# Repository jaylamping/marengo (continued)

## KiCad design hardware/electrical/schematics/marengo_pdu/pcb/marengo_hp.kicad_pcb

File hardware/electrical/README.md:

# Electrical

Power distribution, harnessing, and field bus topology for Marengo.

- [`pdb/`](pdb/) — Power Distribution Board (KiCad schematic, layout, BOM)
- [`wiring/`](wiring/) — Harness runs, CAN layout, connector pinouts

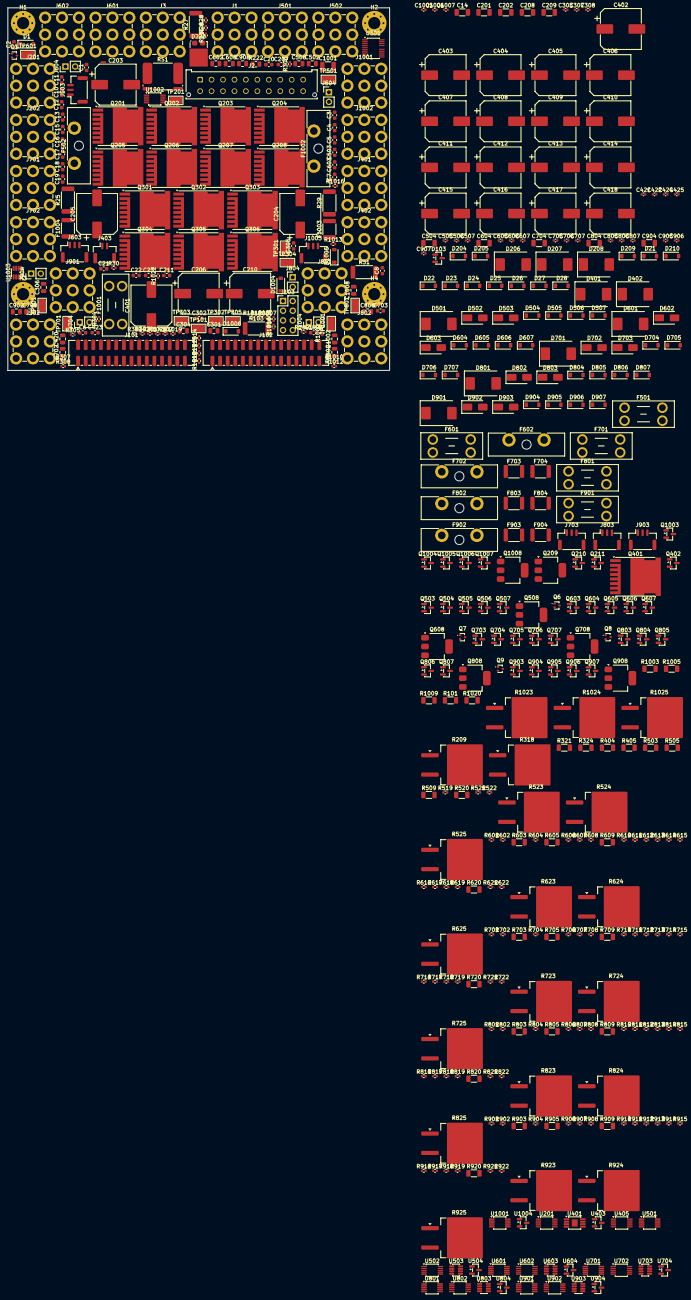
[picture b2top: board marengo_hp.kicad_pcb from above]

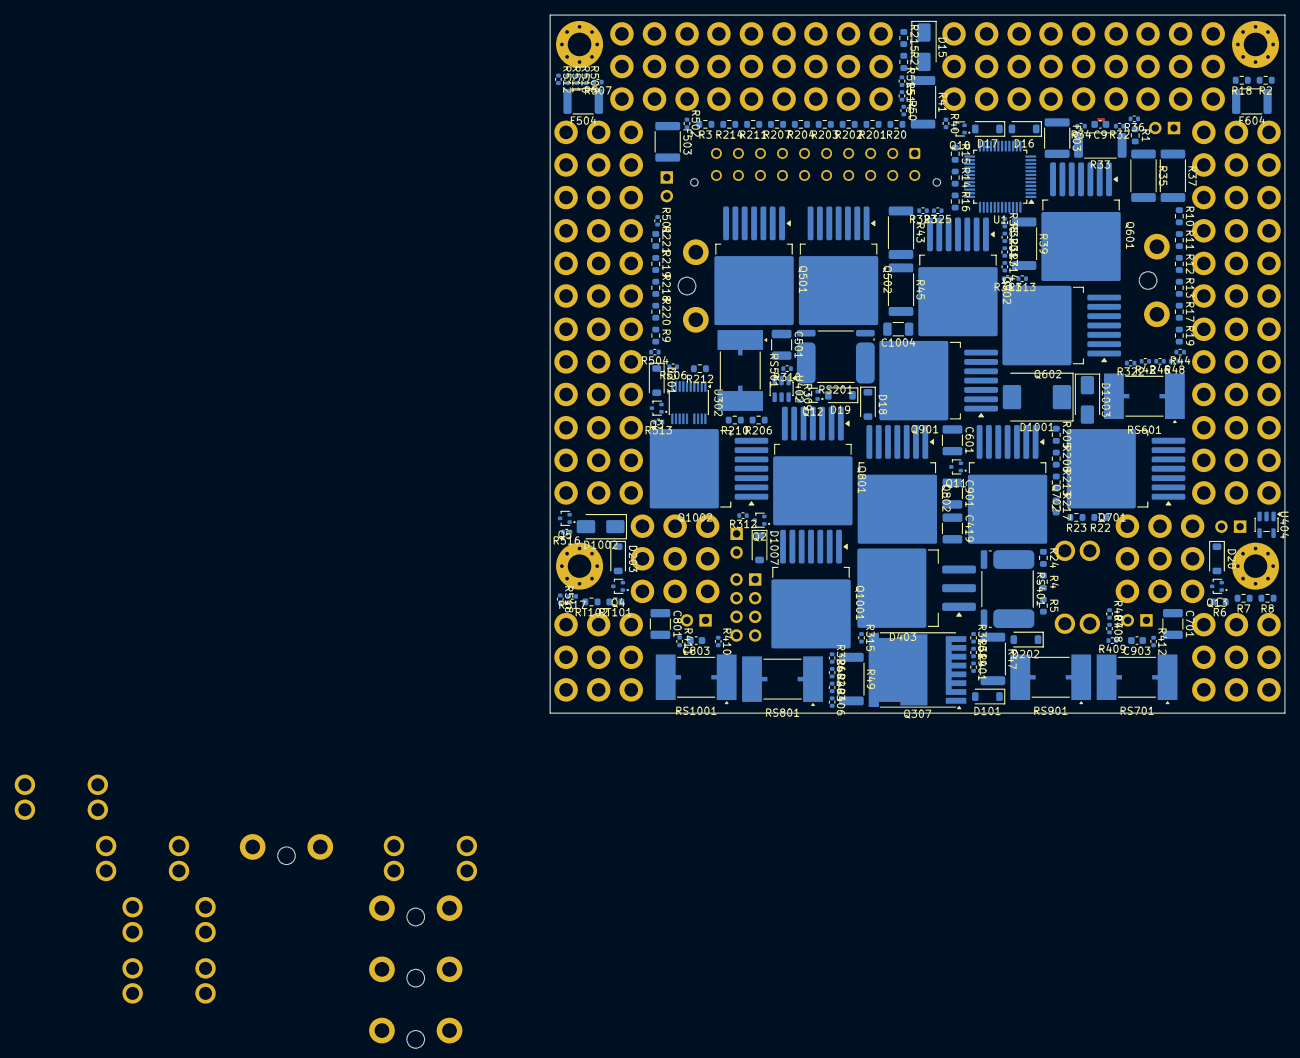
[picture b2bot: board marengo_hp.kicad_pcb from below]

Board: 4 copper layers, 100.0 x 95.0 mm, 653 parts (166 on the bottom side), 373 nets, no tracks yet.

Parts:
C1, C2, C3, C4, C5, C6, C7, C8, C9, C10, C11, C12: 220nF; C_0603_1608Metric
C13, C17, C207: 100nF; C_0603_1608Metric
C14: 1uF 100V; C_1206_3216Metric
C15, C18: 100pF; C_0603_1608Metric
C16: 1uF; C_0603_1608Metric
C19: 2.2uF; C_0603_1608Metric
C20, C21, C22, C211: 1nF; C_0603_1608Metric
C23, C302, C305: 1uF 25V X7R; C_0603_1608Metric
C201, C202, C208, C209: 100nF 100V; C_1206_3216Metric
C203, C204, C205, C206, C210, C401, C402, C403, C404, C405, C406, C407, C408, C409, C410, C411, C412, C413, C414, C415, C416, C417, C418: 100uF 80V HHXF800GRA101MJH0G; CP_Elec_10x14.3
C301, C304, C306, C502, C602, C702, C802, C902, C1002: 100nF 100V; C_0805_2012Metric
C303: 680pF C0G; C_0402_1005Metric
C307, C308: 1nF; C_0402_1005Metric
C419, C501, C601, C701, C801, C901, C1001: 1uF 100V; C_1210_3225Metric
C420: 4.7uF 25V; C_0805_2012Metric
C421: 100pF C0G; C_0402_1005Metric
C422, C424, C425, C505, C506, C507, C605, C606, C607, C705, C706, C707, C805, C806, C807, C905, C906, C907, C1005, C1006, C1007: 100nF; C_0402_1005Metric
C423: 1uF 25V; C_0603_1608Metric
C503, C603, C703, C803, C903, C1003: 100nF C0G; C_0603_1608Metric
C504, C604, C704, C804, C904, C1004: 47nF 100V C0G; C_1206_3216Metric
C508, C608, C708, C808, C908, C1008: 4.7nF 100V; C_0805_2012Metric
D1: BAV19W 120V; D_SOD-123
D15: SS14-E3/61T 40V 1A; D_SMA
D16, D17, D18, D19, D20, D21, D22, D23, D24, D25, D26, D27, D28: BZT52C5V1; D_SOD-123
D101: MMSZ4684 3.3V; D_SOD-123
D103: BAT54C; SOT-23
D201, D203, D204: MMSZ5246B 16V; D_SOD-123
D202, D205, D209, D504, D604, D704, D804, D904, D1004: BAV19W; D_SOD-123
D206, D207, D401, D402: SMDJ58A; D_SMC
D208: SMDJ58CA; D_SMC
D210: MMSZ4685 3.6V; D_SOD-123
D220: V10PM15-M3/I 150V 10A; TO-277A
D403: MBRB30H100CT-E3/81; TO-263-3_TabPin2
D501, D601, D701, D801, D901, D1001: MBRS3100T3G; D_SMC
D502, D503, D602, D603, D702, D703, D802, D803, D902, D903, D1002, D1003: SMAJ58CA; D_SMA
D505, D605, D705, D805, D905, D1005: MMSZ5242B 12V; D_SOD-123
D506, D507, D606, D607, D706, D707, D806, D807, D906, D907, D1006, D1007: MMSZ5246B; D_SOD-123
F501, F601, F701, F801, F901, F1001: 20A 58V 0997020.WXN; Fuseholder_Blade_Mini_Keystone_3568
F502, F602, F702, F802, F902, F1002: leg fuse, format open; Fuseholder_Blade_ATO_Littelfuse_Pudenz_2_Pin
F503, F603, F703, F803, F903, F1003: 0.14A MF-MSMF014/60X; Fuse_1812_4532Metric
F504, F604, F704, F804, F904, F1004: 0.10A MF-MSMF010/60X; Fuse_1812_4532Metric
H1, H2, H3, H4: M3 standoff; MountingHole_3.2mm_M3_Pad_Via
J1, J3: M4 terminal, REDCUBE 74651194R; Wuerth_REDCUBE-THR_WP-THRSH_74651194_THR
J2: 2x10 locking header; Molex_Micro-Fit_3.0_43045-2012_2x10_P3.00mm_Vertical
J101: 2x15 2 mm box, power and logic; Molex_8783230xx_2x15_P2.0mm_Header_Vertical_Polarized
J102: 2x15 2 mm box, CAN and analog; Molex_8783230xx_2x15_P2.0mm_Header_Vertical_Polarized
J103: CAN fault injection, CAN6; PinHeader_2x04_P2.54mm_Vertical
J201: M4 terminal, charger +, 74651194R; Wuerth_REDCUBE-THR_WP-THRSH_74651194_THR
J202: M4 terminal, charger -, 74651194R; Wuerth_REDCUBE-THR_WP-THRSH_74651194_THR
J401: M4 terminal, Arcol HS25 10R +; Wuerth_REDCUBE-THR_WP-THRSH_74651194_THR
J402: M4 terminal, Arcol HS25 10R -; Wuerth_REDCUBE-THR_WP-THRSH_74651194_THR
J403: brake R NTC; JST_GH_SM02B-GHS-TB_1x02-1MP_P1.25mm_Horizontal
J501, J601, J701, J801, J901, J1001: M4 terminal, port +; Wuerth_REDCUBE-THR_WP-THRSH_74651194_THR
J502, J602, J702, J802, J902, J1002: M4 terminal, port -; Wuerth_REDCUBE-THR_WP-THRSH_74651194_THR
J503, J603, J703, J803, J903, J1003: CAN to trunk; JST_GH_SM03B-GHS-TB_1x03-1MP_P1.25mm_Horizontal
J504, J604, J704, J804, J904, J1004: term jumper; PinHeader_1x02_P2.54mm_Vertical
NT1: Net-Tie; NetTie-2_SMD_Pad0.5mm
Q1, Q2, Q3, Q4, Q5, Q6, Q7, Q8, Q9, Q10, Q11, Q12, Q13: SSM3K56FS; SOT-416
Q201, Q202, Q203, Q204, Q205, Q206, Q207, Q208, Q301, Q302, Q303, Q304, Q305, Q306, Q307, Q401: IPT015N10N5; Infineon_PG-HSOF-8-1
Q209: DMP10H400SE; SOT-223-3_TabPin2
Q210, Q402, Q503, Q504, Q506, Q507, Q603, Q604, Q606, Q607, Q703, Q704, Q706, Q707, Q803, Q804, Q806, Q807, Q903, Q904, Q906, Q907, Q1003, Q1004, Q1006, Q1007: BSS123; SOT-23
Q211: MMBT2907A; SOT-23
Q501, Q502, Q601, Q602, Q701, Q702, Q801, Q802, Q901, Q902, Q1001, Q1002: IPB017N10N5LFATMA1; TO-263-7_TabPin4
Q505, Q605, Q705, Q805, Q905, Q1005: MMBTA92 PNP; SOT-23
Q508, Q608, Q708, Q808, Q908, Q1008: DMP10H400SE-13; SOT-223-3_TabPin2
R1: 20R; R_0603_1608Metric
R2, R3, R4, R5, R6, R7, R8, R9, R10, R11, R12, R13, R14, R15, R16, R17: 100R; R_0603_1608Metric
R18, R19, R20, R21, R211, R213, R214: 5.1k; R_0603_1608Metric
R22: 1k; R_0603_1608Metric
R23, R24, R219: 10k; R_0603_1608Metric
R25, R27, R29, R31, R33, R35, R37, R39, R41, R43, R45, R47, R49: 27R 1W 2512; R_2512_6332Metric
R26, R28, R30, R32, R34, R36, R38, R40, R42, R44, R46, R48, R50, R508, R608, R708, R808, R908, R1008: 1k; R_0402_1005Metric
R101, R509, R520, R609, R620, R709, R720, R809, R820, R909, R920, R1009, R1020: 1M; R_1206_3216Metric
R102, R302, R303, R306, R308, R309, R311, R409, R510, R610, R710, R810, R910, R1010: 100k; R_0402_1005Metric
R103: 100R 1W; R_2512_6332Metric
R201, R202, R203, R204, R205, R206, R207, R208: 4.7R; R_0603_1608Metric
R209, R318: 100R PWR263S-35-1000F; TO-263-2
R210, R220: 1M; R_0603_1608Metric
R212, R217, R218: 10M; R_0603_1608Metric
R215: 220R; R_0603_1608Metric
R216, R522, R622, R722, R822, R922, R1022: 10k; R_0402_1005Metric
R221: 62k; R_0603_1608Metric
R222: 15R; R_0805_2012Metric
R301, R307, R412, R514, R614, R714, R814, R914, R1014: 100R; R_0402_1005Metric
R304, R310, R320, R511, R611, R711, R811, R911, R1011: 1M; R_0402_1005Metric
R305: 10.5k 1%; R_0402_1005Metric
R312, R313, R314, R315, R316, R317: 2.2R; R_0402_1005Metric
R319, R410, R411, R501, R502, R512, R513, R601, R602, R612, R613, R701, R702, R712, R713, R801, R802, R812, R813, R901, R902, R912, R913, R1001, R1002, R1012, R1013: 10R; R_0402_1005Metric
R321, R324: 1M 0.1%; R_1206_3216Metric
R322, R325: 56k 0.1%; R_0402_1005Metric
R323, R326, R515, R615, R715, R815, R915, R1015: 49.9R; R_0402_1005Metric
R401: 464k; R_0402_1005Metric
R402: 49.9k; R_0402_1005Metric
R403: 9.09k; R_0402_1005Metric
R404: 499k 0.1%; R_1206_3216Metric
R405: 604k 0.1%; R_1206_3216Metric
R406: 51.1k 0.1%; R_0402_1005Metric
R407: 19.1M; R_0402_1005Metric
R408: 4.7R; R_0402_1005Metric
R503, R603, R703, R803, R903, R1003: 191k; R_1206_3216Metric
R504, R604, R704, R804, R904, R1004: 18.7k; R_0402_1005Metric
R505, R605, R705, R805, R905, R1005: 95.3k; R_1206_3216Metric
R506, R606, R706, R806, R906, R1006: 4.12k; R_0402_1005Metric
R507, R607, R707, R807, R907, R1007: 69.8k; R_0402_1005Metric
R516, R616, R716, R816, R916, R1016: 25.5k 0.1%; R_0402_1005Metric
R517, R617, R717, R817, R917, R1017: 34.0k 0.1%; R_0402_1005Metric
R518, R618, R718, R818, R918, R1018: 2.61k 0.1%; R_0402_1005Metric
R519, R619, R719, R819, R919, R1019: 3.48M; R_0402_1005Metric
R521, R621, R721, R821, R921, R1021: 33k; R_0402_1005Metric
R523, R623, R723, R823, R923, R1023: 150R PWR263S-35-1500F; TO-263-2
R524, R525, R624, R625, R724, R725, R824, R825, R924, R925, R1024, R1025: 56R PWR263S-35-56R0F; TO-263-2
RS1, RS201: 0.3mR CSS4J-4026 5W; R_Shunt_Isabellenhuette_BVR4026
RS401: 2mR CSS4J-4026K-2L00F 6W; R_Shunt_Isabellenhuette_BVR4026
RS501, RS601, RS701, RS801, RS901, RS1001: 3mR WSLP39213L000FEA 5W; WSLP3921_Kelvin
RT101, RT102: 10k B3435; R_0603_1608Metric
TP101, TP301, TP302, TP303, TP304, TP305, TP501, TP601, TP701, TP801, TP901, TP1001: TP; TestPoint_Keystone_5015_Micro_Mini
TP201: VSYS; TestPoint_Keystone_5015_Micro_Mini
U1: BQ76952PFBR; TQFP-48_7x7mm_P0.5mm
U201, U405, U502, U602, U702, U802, U902, U1002: INA228AIDGSR; TSSOP-10_3x3mm_P0.5mm
U301, U302: TPS48100QDGXRQ1; TPS48100_DGX_VSSOP-19
U401: TPS7A4001DGNR; HVSSOP-8-1EP_3x3mm_P0.65mm_EP1.57x1.89mm
U402: TLV1805DBVR; SOT-23-6
U403: LM4040AIM3-2.5; SOT-23
U404: UCC27517DBVR; SOT-23-5
U501, U601, U701, U801, U901, U1001: LM5069MMX-1; MSOP-10_3x3mm_P0.5mm
U503, U603, U703, U803, U903, U1003: INA241A1IDDFR; SOT-23-8
U504, U604, U704, U804, U904, U1004: TL431BIDBZR; SOT-23

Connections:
+3V3_HP: C207.1, C425.1, C506.1, C507.1, C606.1, C607.1, C706.1, C707.1, C806.1, C807.1, C906.1, C907.1, C1006.1, C1007.1, J101.28, R303.2, R309.2, U201.6, U405.2, U405.6, U502.6, U503.6, U503.7, U602.2, U602.6, U603.6, U603.7, U702.1, U702.6, U703.6, U703.7, U802.6, U803.6, U803.7, U902.1, U902.6, U903.6, U903.7, U1002.1, U1002.2, U1002.6, U1003.6, U1003.7
/HP_power_board/BOARD_NTC: RT101.1, U1.28
/HP_power_board/CHG_GATE: R211.1, U1.45
/HP_power_board/DFETOFF: D103.3, R102.1, U1.30
/HP_power_board/DSG_GATE: D202.1, R213.1, U1.43
/HP_power_board/FI_V: J103.8, R103.2
/HP_power_board/PACK_PRESENT_N: D101.1, D103.1, J2.13, R101.2
/HP_power_board/PACK_TOP: C201.1, C203.1, C204.1, C205.1, C206.1, D1.2, D201.2, D206.1, J1.1, Q201.2, Q202.2, Q203.2, Q204.2, R101.1, R212.2
/HP_power_board/PDSG: Q209.1, R210.2, U1.39
/HP_power_board/V_PORT6: D1007.1, F1001.2, F1002.2, J1001.1, Q1008.3, R103.1, R1014.1, R1016.1, R1020.1, R1022.1, TP1001.1
/HP_power_board/bms_fets_precharge/CD: Q201.3, Q202.3, Q203.3, Q204.3, Q205.3, Q206.3, Q207.3, Q208.3, Q209.3, R210.1
/HP_power_board/bms_fets_precharge/CHG_G: D201.1, R201.1, R202.1, R203.1, R204.1, R211.2, R212.1
/HP_power_board/bms_fets_precharge/CHG_IN: D208.2, D209.2, D220.1, D220.2, J201.1
/HP_power_board/bms_fets_precharge/DSG_G: D203.1, Q210.3, Q211.2, R205.1, R206.1, R207.1, R208.1, R214.2, R216.2, R217.1
/HP_power_board/bms_fets_precharge/DSG_OFF_B: Q211.1, R215.2, R216.1
/HP_power_board/bms_fets_precharge/DSG_OFF_C: Q211.3, R222.1
/HP_power_board/bms_fets_precharge/DSG_OUT: C202.2, D203.2, D204.2, Q205.2, Q206.2, Q207.2, Q208.2, Q210.2, R209.3, R217.2, R218.2, R222.2, RS201.1
/HP_power_board/bms_fets_precharge/PDSG_R: Q209.2, R209.1
/HP_power_board/estop_banks/BST_A: C302.1, U301.12
/HP_power_board/estop_banks/BST_B: C305.1, U302.12
/HP_power_board/estop_banks/FLT_B: R309.1, TP302.1, U302.5
/HP_power_board/estop_banks/G2_B: R319.1, U302.11
/HP_power_board/estop_banks/G2_G: Q307.1, R319.2, R320.1
/HP_power_board/estop_banks/GA0: Q301.1, R312.2
/HP_power_board/estop_banks/GA1: Q303.1, R313.2
/HP_power_board/estop_banks/GA2: Q305.1, R314.2
/HP_power_board/estop_banks/GATE_A: R304.1, R312.1, R313.1, R314.1, U301.14, U301.15
/HP_power_board/estop_banks/GATE_B: R310.1, R315.1, R316.1, R317.1, U302.14, U302.15
/HP_power_board/estop_banks/GB0: Q302.1, R315.2
/HP_power_board/estop_banks/GB1: Q304.1, R316.2
/HP_power_board/estop_banks/GB2: Q306.1, R317.2
/HP_power_board/estop_banks/ISCP_A: R305.1, U301.8
/HP_power_board/estop_banks/MID_DIV: C307.1, R321.2, R322.1, R323.1
/HP_power_board/estop_banks/PRE_D: Q307.3, R318.3
/HP_power_board/estop_banks/TMR_A: C303.1, R306.1, U301.9
/HP_power_board/estop_banks/VMOT_DIV: C308.1, R324.2, R325.1, R326.1
/HP_power_board/estop_banks/VS_A: C301.1, R301.2, U301.20
/HP_power_board/estop_banks/VS_B: C304.1, R307.2, U302.17, U302.18, U302.20
/HP_power_board/pack_input_shunt_afe/B0: D16.2, J2.4, Q1.2, R14.1, R24.1
/HP_power_board/pack_input_shunt_afe/B1: D17.2, J2.14, Q2.2, R13.1, R25.1
/HP_power_board/pack_input_shunt_afe/B2: D18.2, J2.5, Q3.2, R12.1, R27.1
/HP_power_board/pack_input_shunt_afe/B3: D19.2, J2.15, Q4.2, R11.1, R29.1
/HP_power_board/pack_input_shunt_afe/B4: D20.2, J2.6, Q5.2, R10.1, R31.1
/HP_power_board/pack_input_shunt_afe/B5: D21.2, J2.16, Q6.2, R9.1, R33.1
/HP_power_board/pack_input_shunt_afe/B6: D22.2, J2.7, Q7.2, R8.1, R35.1
/HP_power_board/pack_input_shunt_afe/B7: D23.2, J2.17, Q8.2, R7.1, R37.1
/HP_power_board/pack_input_shunt_afe/B8: D24.2, J2.8, Q9.2, R6.1, R39.1
/HP_power_board/pack_input_shunt_afe/B9: D25.2, J2.18, Q10.2, R5.1, R41.1
/HP_power_board/pack_input_shunt_afe/B10: D26.2, J2.9, Q11.2, R4.1, R43.1
/HP_power_board/pack_input_shunt_afe/B11: D27.2, J2.19, Q12.2, R3.1, R45.1
/HP_power_board/pack_input_shunt_afe/B12: D28.2, J2.10, Q13.2, R2.1, R47.1
/HP_power_board/pack_input_shunt_afe/B13: J2.20, R1.1, R49.1
/HP_power_board/pack_input_shunt_afe/BAT: C14.1, C15.1, C16.1, R15.2, U1.47
/HP_power_board/pack_input_shunt_afe/BAT-: J3.1, NT1.1, R24.2, RS1.1
/HP_power_board/pack_input_shunt_afe/BD1: Q1.3, R25.2
/HP_power_board/pack_input_shunt_afe/BD2: Q2.3, R27.2
/HP_power_board/pack_input_shunt_afe/BD3: Q3.3, R29.2
/HP_power_board/pack_input_shunt_afe/BD4: Q4.3, R31.2
/HP_power_board/pack_input_shunt_afe/BD5: Q5.3, R33.2
/HP_power_board/pack_input_shunt_afe/BD6: Q6.3, R35.2
/HP_power_board/pack_input_shunt_afe/BD7: Q7.3, R37.2
/HP_power_board/pack_input_shunt_afe/BD8: Q8.3, R39.2
/HP_power_board/pack_input_shunt_afe/BD9: Q9.3, R41.2
/HP_power_board/pack_input_shunt_afe/BD10: Q10.3, R43.2
/HP_power_board/pack_input_shunt_afe/BD11: Q11.3, R45.2
/HP_power_board/pack_input_shunt_afe/BD12: Q12.3, R47.2
/HP_power_board/pack_input_shunt_afe/BD13: Q13.3, R49.2
/HP_power_board/pack_input_shunt_afe/BG1: D16.1, Q1.1, R26.1
/HP_power_board/pack_input_shunt_afe/BG2: D17.1, Q2.1, R28.1
/HP_power_board/pack_input_shunt_afe/BG3: D18.1, Q3.1, R30.1
/HP_power_board/pack_input_shunt_afe/BG4: D19.1, Q4.1, R32.1
/HP_power_board/pack_input_shunt_afe/BG5: D20.1, Q5.1, R34.1
/HP_power_board/pack_input_shunt_afe/BG6: D21.1, Q6.1, R36.1
/HP_power_board/pack_input_shunt_afe/BG7: D22.1, Q7.1, R38.1
/HP_power_board/pack_input_shunt_afe/BG8: D23.1, Q8.1, R40.1
/HP_power_board/pack_input_shunt_afe/BG9: D24.1, Q9.1, R42.1
/HP_power_board/pack_input_shunt_afe/BG10: D25.1, Q10.1, R44.1
/HP_power_board/pack_input_shunt_afe/BG11: D26.1, Q11.1, R46.1
/HP_power_board/pack_input_shunt_afe/BG12: D27.1, Q12.1, R48.1
/HP_power_board/pack_input_shunt_afe/BG13: D28.1, Q13.1, R50.1
/HP_power_board/pack_input_shunt_afe/CP1: C16.2, U1.46
/HP_power_board/pack_input_shunt_afe/LD_S: R20.1, U1.41
/HP_power_board/pack_input_shunt_afe/NTC1: C20.1, J2.1, U1.21
/HP_power_board/pack_input_shunt_afe/NTC2: C21.1, J2.11, U1.23
/HP_power_board/pack_input_shunt_afe/NTC3: C22.1, J2.2, U1.29
/HP_power_board/pack_input_shunt_afe/PACK_S: R18.1, U1.42
/HP_power_board/pack_input_shunt_afe/SRN: R17.1, RS1.3
/HP_power_board/pack_input_shunt_afe/SRN_F: C17.2, C18.2, R17.2, U1.20
/HP_power_board/pack_input_shunt_afe/SRP: R16.1, RS1.2
/HP_power_board/pack_input_shunt_afe/SRP_F: C17.1, C18.1, R16.2, U1.18
/HP_power_board/pack_input_shunt_afe/TS2_F: R23.1, U1.22
/HP_power_board/pack_input_shunt_afe/VC0: C13.2, C23.1, D15.1, R14.2, R26.2, U1.16
/HP_power_board/pack_input_shunt_afe/VC1: C12.2, C13.1, R13.2, R28.2, U1.15
/HP_power_board/pack_input_shunt_afe/VC2: C11.2, C12.1, R12.2, R30.2, U1.14
/HP_power_board/pack_input_shunt_afe/VC3: C10.2, C11.1, R11.2, R32.2, U1.13
/HP_power_board/pack_input_shunt_afe/VC4: C9.2, C10.1, R10.2, R34.2, U1.12
/HP_power_board/pack_input_shunt_afe/VC5: C8.2, C9.1, R9.2, R36.2, U1.11
/HP_power_board/pack_input_shunt_afe/VC6: C7.2, C8.1, R8.2, R38.2, U1.10
/HP_power_board/pack_input_shunt_afe/VC7: C6.2, C7.1, R7.2, R40.2, U1.9
/HP_power_board/pack_input_shunt_afe/VC8: C5.2, C6.1, R6.2, R42.2, U1.8
/HP_power_board/pack_input_shunt_afe/VC9: C4.2, C5.1, R5.2, R44.2, U1.7
/HP_power_board/pack_input_shunt_afe/VC10: C3.2, C4.1, R4.2, R46.2, U1.6
/HP_power_board/pack_input_shunt_afe/VC11: C2.2, C3.1, R3.2, R48.2, U1.5
/HP_power_board/pack_input_shunt_afe/VC12: C1.2, C2.1, R2.2, R50.2, U1.1, U1.2, U1.3, U1.4
/HP_power_board/pack_input_shunt_afe/VC16: C1.1, R1.2, U1.48
/HP_power_board/port_1_L_ARM/CAN_REF: F503.1, J503.3
/HP_power_board/port_1_L_ARM/CAS_D: Q507.3, R521.1
/HP_power_board/port_1_L_ARM/CAS_G: D506.1, Q507.1, R520.2
/HP_power_board/port_1_L_ARM/CDV: C504.1, D504.1, Q505.2
/HP_power_board/port_1_L_ARM/CDV_B: Q505.1, R508.2
/HP_power_board/port_1_L_ARM/EN_INV: D505.1, Q503.1, Q504.3, R509.2
/HP_power_board/port_1_L_ARM/EN_S: Q504.2, Q506.3
/HP_power_board/port_1_L_ARM/G1: Q501.1, R501.2
/HP_power_board/port_1_L_ARM/G2: Q502.1, R502.2
/HP_power_board/port_1_L_ARM/GATE: D504.2, R501.1, R502.1, R508.1, U501.10
/HP_power_board/port_1_L_ARM/IM_RAW: R515.1, U503.5
/HP_power_board/port_1_L_ARM/IN_N: C505.2, R513.2, U502.9
/HP_power_board/port_1_L_ARM/IN_P: C505.1, R512.2, U502.10
/HP_power_board/port_1_L_ARM/OVLO: R505.2, R506.1, U501.4
/HP_power_board/port_1_L_ARM/PD: Q508.2, R519.1, R523.1
/HP_power_board/port_1_L_ARM/PG: D507.2, Q508.1, R521.2, R522.2
/HP_power_board/port_1_L_ARM/PWR: R507.1, U501.7
/HP_power_board/port_1_L_ARM/Q_D: Q501.4, Q502.4, RS501.4
/HP_power_board/port_1_L_ARM/SH_N: R513.1, RS501.3, U501.1, U503.1
/HP_power_board/port_1_L_ARM/SH_P: C502.1, R512.1, RS501.2, U501.2, U503.8
/HP_power_board/port_1_L_ARM/TERM_J: F504.2, J504.1
/HP_power_board/port_1_L_ARM/TERM_M: C508.1, R524.3, R525.1
/HP_power_board/port_1_L_ARM/TERM_P: F504.1, R525.3
/HP_power_board/port_1_L_ARM/TIMER: C503.1, U501.6
/HP_power_board/port_1_L_ARM/TL_K: Q507.2, U504.1
/HP_power_board/port_1_L_ARM/TL_M: R516.2, R517.1
/HP_power_board/port_1_L_ARM/TL_R: R517.2, R518.1, R519.2, U504.2
/HP_power_board/port_1_L_ARM/UVLO: Q503.3, R503.2, R504.1, U501.3
/HP_power_board/port_1_L_ARM/VB_F: R514.2, U502.8
/HP_power_board/port_1_L_ARM/V_OUT: D501.1, F501.1, F502.1, Q501.2, Q501.3, Q501.5, Q501.6, Q501.7, Q502.2, Q502.3, Q502.5, Q502.6, Q502.7, U501.9
/HP_power_board/port_1_L_ARM/V_PORT: D507.1, F501.2, F502.2, J501.1, Q508.3, R514.1, R516.1, R520.1, R522.1, TP501.1
/HP_power_board/port_2_R_ARM/CAN_REF: F603.1, J603.3
/HP_power_board/port_2_R_ARM/CAS_D: Q607.3, R621.1
/HP_power_board/port_2_R_ARM/CAS_G: D606.1, Q607.1, R620.2
/HP_power_board/port_2_R_ARM/CDV: C604.1, D604.1, Q605.2
/HP_power_board/port_2_R_ARM/CDV_B: Q605.1, R608.2
/HP_power_board/port_2_R_ARM/EN_INV: D605.1, Q603.1, Q604.3, R609.2
/HP_power_board/port_2_R_ARM/EN_S: Q604.2, Q606.3
/HP_power_board/port_2_R_ARM/G1: Q601.1, R601.2
/HP_power_board/port_2_R_ARM/G2: Q602.1, R602.2
/HP_power_board/port_2_R_ARM/GATE: D604.2, R601.1, R602.1, R608.1, U601.10
/HP_power_board/port_2_R_ARM/IM_RAW: R615.1, U603.5
/HP_power_board/port_2_R_ARM/IN_N: C605.2, R613.2, U602.9
/HP_power_board/port_2_R_ARM/IN_P: C605.1, R612.2, U602.10
/HP_power_board/port_2_R_ARM/OVLO: R605.2, R606.1, U601.4
/HP_power_board/port_2_R_ARM/PD: Q608.2, R619.1, R623.1
/HP_power_board/port_2_R_ARM/PG: D607.2, Q608.1, R621.2, R622.2
/HP_power_board/port_2_R_ARM/PWR: R607.1, U601.7
/HP_power_board/port_2_R_ARM/Q_D: Q601.4, Q602.4, RS601.4
/HP_power_board/port_2_R_ARM/SH_N: R613.1, RS601.3, U601.1, U603.1
/HP_power_board/port_2_R_ARM/SH_P: C602.1, R612.1, RS601.2, U601.2, U603.8
/HP_power_board/port_2_R_ARM/TERM_J: F604.2, J604.1
/HP_power_board/port_2_R_ARM/TERM_M: C608.1, R624.3, R625.1
/HP_power_board/port_2_R_ARM/TERM_P: F604.1, R625.3
/HP_power_board/port_2_R_ARM/TIMER: C603.1, U601.6
/HP_power_board/port_2_R_ARM/TL_K: Q607.2, U604.1
/HP_power_board/port_2_R_ARM/TL_M: R616.2, R617.1
/HP_power_board/port_2_R_ARM/TL_R: R617.2, R618.1, R619.2, U604.2
/HP_power_board/port_2_R_ARM/UVLO: Q603.3, R603.2, R604.1, U601.3
/HP_power_board/port_2_R_ARM/VB_F: R614.2, U602.8
/HP_power_board/port_2_R_ARM/V_OUT: D601.1, F601.1, F602.1, Q601.2, Q601.3, Q601.5, Q601.6, Q601.7, Q602.2, Q602.3, Q602.5, Q602.6, Q602.7, U601.9
/HP_power_board/port_2_R_ARM/V_PORT: D607.1, F601.2, F602.2, J601.1, Q608.3, R614.1, R616.1, R620.1, R622.1, TP601.1
/HP_power_board/port_3_WAIST/CAN_REF: F703.1, J703.3
/HP_power_board/port_3_WAIST/CAS_D: Q707.3, R721.1
/HP_power_board/port_3_WAIST/CAS_G: D706.1, Q707.1, R720.2
/HP_power_board/port_3_WAIST/CDV: C704.1, D704.1, Q705.2
/HP_power_board/port_3_WAIST/CDV_B: Q705.1, R708.2
/HP_power_board/port_3_WAIST/EN_INV: D705.1, Q703.1, Q704.3, R709.2
/HP_power_board/port_3_WAIST/EN_S: Q704.2, Q706.3
/HP_power_board/port_3_WAIST/G1: Q701.1, R701.2
/HP_power_board/port_3_WAIST/G2: Q702.1, R702.2
/HP_power_board/port_3_WAIST/GATE: D704.2, R701.1, R702.1, R708.1, U701.10
/HP_power_board/port_3_WAIST/IM_RAW: R715.1, U703.5
/HP_power_board/port_3_WAIST/IN_N: C705.2, R713.2, U702.9
/HP_power_board/port_3_WAIST/IN_P: C705.1, R712.2, U702.10
/HP_power_board/port_3_WAIST/OVLO: R705.2, R706.1, U701.4
/HP_power_board/port_3_WAIST/PD: Q708.2, R719.1, R723.1
/HP_power_board/port_3_WAIST/PG: D707.2, Q708.1, R721.2, R722.2
/HP_power_board/port_3_WAIST/PWR: R707.1, U701.7
/HP_power_board/port_3_WAIST/Q_D: Q701.4, Q702.4, RS701.4
/HP_power_board/port_3_WAIST/SH_N: R713.1, RS701.3, U701.1, U703.1
/HP_power_board/port_3_WAIST/SH_P: C702.1, R712.1, RS701.2, U701.2, U703.8
/HP_power_board/port_3_WAIST/TERM_J: F704.2, J704.1
/HP_power_board/port_3_WAIST/TERM_M: C708.1, R724.3, R725.1
/HP_power_board/port_3_WAIST/TERM_P: F704.1, R725.3
/HP_power_board/port_3_WAIST/TIMER: C703.1, U701.6
/HP_power_board/port_3_WAIST/TL_K: Q707.2, U704.1
/HP_power_board/port_3_WAIST/TL_M: R716.2, R717.1
/HP_power_board/port_3_WAIST/TL_R: R717.2, R718.1, R719.2, U704.2
/HP_power_board/port_3_WAIST/UVLO: Q703.3, R703.2, R704.1, U701.3
/HP_power_board/port_3_WAIST/VB_F: R714.2, U702.8
/HP_power_board/port_3_WAIST/V_OUT: D701.1, F701.1, F702.1, Q701.2, Q701.3, Q701.5, Q701.6, Q701.7, Q702.2, Q702.3, Q702.5, Q702.6, Q702.7, U701.9
/HP_power_board/port_3_WAIST/V_PORT: D707.1, F701.2, F702.2, J701.1, Q708.3, R714.1, R716.1, R720.1, R722.1, TP701.1
/HP_power_board/port_4_L_LEG/CAN_REF: F803.1, J803.3
/HP_power_board/port_4_L_LEG/CAS_D: Q807.3, R821.1
/HP_power_board/port_4_L_LEG/CAS_G: D806.1, Q807.1, R820.2
/HP_power_board/port_4_L_LEG/CDV: C804.1, D804.1, Q805.2
/HP_power_board/port_4_L_LEG/CDV_B: Q805.1, R808.2
/HP_power_board/port_4_L_LEG/EN_INV: D805.1, Q803.1, Q804.3, R809.2
/HP_power_board/port_4_L_LEG/EN_S: Q804.2, Q806.3
/HP_power_board/port_4_L_LEG/G1: Q801.1, R801.2
/HP_power_board/port_4_L_LEG/G2: Q802.1, R802.2
/HP_power_board/port_4_L_LEG/GATE: D804.2, R801.1, R802.1, R808.1, U801.10
/HP_power_board/port_4_L_LEG/IM_RAW: R815.1, U803.5
/HP_power_board/port_4_L_LEG/IN_N: C805.2, R813.2, U802.9
/HP_power_board/port_4_L_LEG/IN_P: C805.1, R812.2, U802.10
/HP_power_board/port_4_L_LEG/OVLO: R805.2, R806.1, U801.4
/HP_power_board/port_4_L_LEG/PD: Q808.2, R819.1, R823.1
/HP_power_board/port_4_L_LEG/PG: D807.2, Q808.1, R821.2, R822.2
/HP_power_board/port_4_L_LEG/PWR: R807.1, U801.7
/HP_power_board/port_4_L_LEG/Q_D: Q801.4, Q802.4, RS801.4
/HP_power_board/port_4_L_LEG/SH_N: R813.1, RS801.3, U801.1, U803.1
/HP_power_board/port_4_L_LEG/SH_P: C802.1, R812.1, RS801.2, U801.2, U803.8
/HP_power_board/port_4_L_LEG/TERM_J: F804.2, J804.1
/HP_power_board/port_4_L_LEG/TERM_M: C808.1, R824.3, R825.1
/HP_power_board/port_4_L_LEG/TERM_P: F804.1, R825.3
/HP_power_board/port_4_L_LEG/TIMER: C803.1, U801.6
/HP_power_board/port_4_L_LEG/TL_K: Q807.2, U804.1
/HP_power_board/port_4_L_LEG/TL_M: R816.2, R817.1
/HP_power_board/port_4_L_LEG/TL_R: R817.2, R818.1, R819.2, U804.2
/HP_power_board/port_4_L_LEG/UVLO: Q803.3, R803.2, R804.1, U801.3
/HP_power_board/port_4_L_LEG/VB_F: R814.2, U802.8
/HP_power_board/port_4_L_LEG/V_OUT: D801.1, F801.1, F802.1, Q801.2, Q801.3, Q801.5, Q801.6, Q801.7, Q802.2, Q802.3, Q802.5, Q802.6, Q802.7, U801.9
/HP_power_board/port_4_L_LEG/V_PORT: D807.1, F801.2, F802.2, J801.1, Q808.3, R814.1, R816.1, R820.1, R822.1, TP801.1
/HP_power_board/port_5_R_LEG/CAN_REF: F903.1, J903.3
/HP_power_board/port_5_R_LEG/CAS_D: Q907.3, R921.1
/HP_power_board/port_5_R_LEG/CAS_G: D906.1, Q907.1, R920.2
/HP_power_board/port_5_R_LEG/CDV: C904.1, D904.1, Q905.2
/HP_power_board/port_5_R_LEG/CDV_B: Q905.1, R908.2
/HP_power_board/port_5_R_LEG/EN_INV: D905.1, Q903.1, Q904.3, R909.2
/HP_power_board/port_5_R_LEG/EN_S: Q904.2, Q906.3
/HP_power_board/port_5_R_LEG/G1: Q901.1, R901.2
/HP_power_board/port_5_R_LEG/G2: Q902.1, R902.2
/HP_power_board/port_5_R_LEG/GATE: D904.2, R901.1, R902.1, R908.1, U901.10
/HP_power_board/port_5_R_LEG/IM_RAW: R915.1, U903.5
/HP_power_board/port_5_R_LEG/IN_N: C905.2, R913.2, U902.9
/HP_power_board/port_5_R_LEG/IN_P: C905.1, R912.2, U902.10
/HP_power_board/port_5_R_LEG/OVLO: R905.2, R906.1, U901.4
/HP_power_board/port_5_R_LEG/PD: Q908.2, R919.1, R923.1
/HP_power_board/port_5_R_LEG/PG: D907.2, Q908.1, R921.2, R922.2
/HP_power_board/port_5_R_LEG/PWR: R907.1, U901.7
/HP_power_board/port_5_R_LEG/Q_D: Q901.4, Q902.4, RS901.4
/HP_power_board/port_5_R_LEG/SH_N: R913.1, RS901.3, U901.1, U903.1
/HP_power_board/port_5_R_LEG/SH_P: C902.1, R912.1, RS901.2, U901.2, U903.8
/HP_power_board/port_5_R_LEG/TERM_J: F904.2, J904.1
/HP_power_board/port_5_R_LEG/TERM_M: C908.1, R924.3, R925.1
/HP_power_board/port_5_R_LEG/TERM_P: F904.1, R925.3
/HP_power_board/port_5_R_LEG/TIMER: C903.1, U901.6
/HP_power_board/port_5_R_LEG/TL_K: Q907.2, U904.1
/HP_power_board/port_5_R_LEG/TL_M: R916.2, R917.1
/HP_power_board/port_5_R_LEG/TL_R: R917.2, R918.1, R919.2, U904.2
/HP_power_board/port_5_R_LEG/UVLO: Q903.3, R903.2, R904.1, U901.3
/HP_power_board/port_5_R_LEG/VB_F: R914.2, U902.8
/HP_power_board/port_5_R_LEG/V_OUT: D901.1, F901.1, F902.1, Q901.2, Q901.3, Q901.5, Q901.6, Q901.7, Q902.2, Q902.3, Q902.5, Q902.6, Q902.7, U901.9
/HP_power_board/port_5_R_LEG/V_PORT: D907.1, F901.2, F902.2, J901.1, Q908.3, R914.1, R916.1, R920.1, R922.1, TP901.1
/HP_power_board/port_6_AUX/CAN_REF: F1003.1, J1003.3
/HP_power_board/port_6_AUX/CAS_D: Q1007.3, R1021.1
/HP_power_board/port_6_AUX/CAS_G: D1006.1, Q1007.1, R1020.2
/HP_power_board/port_6_AUX/CDV: C1004.1, D1004.1, Q1005.2
/HP_power_board/port_6_AUX/CDV_B: Q1005.1, R1008.2
/HP_power_board/port_6_AUX/EN_INV: D1005.1, Q1003.1, Q1004.3, R1009.2
/HP_power_board/port_6_AUX/EN_S: Q1004.2, Q1006.3
/HP_power_board/port_6_AUX/G1: Q1001.1, R1001.2
/HP_power_board/port_6_AUX/G2: Q1002.1, R1002.2
/HP_power_board/port_6_AUX/GATE: D1004.2, R1001.1, R1002.1, R1008.1, U1001.10
/HP_power_board/port_6_AUX/IM_RAW: R1015.1, U1003.5
/HP_power_board/port_6_AUX/IN_N: C1005.2, R1013.2, U1002.9
/HP_power_board/port_6_AUX/IN_P: C1005.1, R1012.2, U1002.10
/HP_power_board/port_6_AUX/OVLO: R1005.2, R1006.1, U1001.4
/HP_power_board/port_6_AUX/PD: Q1008.2, R1019.1, R1023.1
/HP_power_board/port_6_AUX/PG: D1007.2, Q1008.1, R1021.2, R1022.2
/HP_power_board/port_6_AUX/PWR: R1007.1, U1001.7
/HP_power_board/port_6_AUX/Q_D: Q1001.4, Q1002.4, RS1001.4
/HP_power_board/port_6_AUX/SH_N: R1013.1, RS1001.3, U1001.1, U1003.1
/HP_power_board/port_6_AUX/SH_P: C1002.1, R1012.1, RS1001.2, U1001.2, U1003.8
/HP_power_board/port_6_AUX/TERM_J: F1004.2, J1004.1
/HP_power_board/port_6_AUX/TERM_M: C1008.1, R1024.3, R1025.1
/HP_power_board/port_6_AUX/TERM_P: F1004.1, R1025.3
/HP_power_board/port_6_AUX/TIMER: C1003.1, U1001.6
/HP_power_board/port_6_AUX/TL_K: Q1007.2, U1004.1
/HP_power_board/port_6_AUX/TL_M: R1016.2, R1017.1
/HP_power_board/port_6_AUX/TL_R: R1017.2, R1018.1, R1019.2, U1004.2
/HP_power_board/port_6_AUX/UVLO: Q1003.3, R1003.2, R1004.1, U1001.3
/HP_power_board/port_6_AUX/VB_F: R1014.2, U1002.8
/HP_power_board/port_6_AUX/V_OUT: D1001.1, F1001.1, F1002.1, Q1001.2, Q1001.3, Q1001.5, Q1001.6, Q1001.7, Q1002.2, Q1002.3, Q1002.5, Q1002.6, Q1002.7, U1001.9
/HP_power_board/vmot_bulk_clamp/CL_D: D403.1, D403.3, J402.1, Q401.3
/HP_power_board/vmot_bulk_clamp/CL_DIV: R404.2, R405.1
/HP_power_board/vmot_bulk_clamp/CL_G: Q401.1, R408.2, R409.1
/HP_power_board/vmot_bulk_clamp/CL_GDRV: R408.1, U404.5
/HP_power_board/vmot_bulk_clamp/CL_IN: C424.2, R411.2, U405.9
/HP_power_board/vmot_bulk_clamp/CL_IP: C424.1, R410.2, U405.10
/HP_power_board/vmot_bulk_clamp/CL_OUT: Q402.1, R407.1, U402.1, U404.3
/HP_power_board/vmot_bulk_clamp/CL_S: Q401.2, RS401.1
/HP_power_board/vmot_bulk_clamp/CL_SENSE: C421.1, R405.2, R406.1, R407.2, U402.4
/HP_power_board/vmot_bulk_clamp/CL_SN: R411.1, RS401.3
/HP_power_board/vmot_bulk_clamp/CL_SP: R410.1, RS401.2
/HP_power_board/vmot_bulk_clamp/CL_VB: R412.2, U405.8
/HP_power_board/vmot_bulk_clamp/FB12: R401.2, R402.1, U401.2
/HP_power_board/vmot_bulk_clamp/VREF_CL: R403.2, U402.3, U403.1
AFE_ALERT: J101.23, U1.25
AFE_DFETOFF_SUP: D103.2, J101.24
AFE_RST_SHUT: J101.25, R22.1, U1.33
BANK_B_CLOSE: J101.14, R311.1, U302.3
CAN1_H: D502.1, J102.1, J503.1, R524.1
CAN1_L: D503.1, J102.2, J503.2, J504.2
CAN2_H: D602.1, J102.4, J603.1, R624.1
CAN2_L: D603.1, J102.5, J603.2, J604.2
CAN3_H: D702.1, J102.7, J703.1, R724.1
CAN3_L: D703.1, J102.8, J703.2, J704.2
CAN4_H: D802.1, J102.10, J803.1, R824.1
CAN4_L: D803.1, J102.11, J803.2, J804.2
CAN5_H: D902.1, J102.13, J903.1, R924.1
CAN5_L: D903.1, J102.14, J903.2, J904.2
CAN6_H: D1002.1, J102.16, J103.1, J103.3, J103.7, J1003.1, R1024.1
CAN6_L: D1003.1, J102.17, J103.2, J103.5, J1003.2, J1004.2
CHARGER_PRESENT: C211.1, D210.1, J101.30, R220.2, R221.1
CLAMP_STATUS: J101.29, Q402.3
ESTOP_EN_A: J101.10, R302.1, U301.1, U301.3
ESTOP_EN_B: J101.11, R308.1, U302.1, U302.2
FLT_A: J102.3, R303.1, TP301.1, U301.5
GND: C203.2, C204.2, C205.2, C206.2, C207.2, C209.2, C210.2, C211.2, C301.2, C303.2, C304.2, C306.2, C307.2, C308.2, C401.2, C402.2, C403.2, C404.2, C405.2, C406.2, C407.2, C408.2, C409.2, C410.2, C411.2, C412.2, C413.2, C414.2, C415.2, C416.2, C417.2, C418.2, C419.2, C420.2, C421.2, C422.2, C423.2, C425.2, C501.2, C502.2, C503.2, C504.2, C506.2, C507.2, C508.2, C601.2, C602.2, C603.2, C604.2, C606.2, C607.2, C608.2, C701.2, C702.2, C703.2, C704.2, C706.2, C707.2, C708.2, C801.2, C802.2, C803.2, C804.2, C806.2, C807.2, C808.2, C901.2, C902.2, C903.2, C904.2, C906.2, C907.2, C908.2, C1001.2, C1002.2, C1003.2, C1004.2, C1006.2, C1007.2, C1008.2, D205.2, D206.2, D207.2, D208.1, D210.2, D401.2, D402.2, D501.2, D502.2, D503.2, D505.2, D506.2, D601.2, D602.2, D603.2, D605.2, D606.2, D701.2, D702.2, D703.2, D705.2, D706.2, D801.2, D802.2, D803.2, D805.2, D806.2, D901.2, D902.2, D903.2, D905.2, D906.2, D1001.2, D1002.2, D1003.2, D1005.2, D1006.2, F503.2, F603.2, F703.2, F803.2, F903.2, F1003.2, J101.7, J101.8, J101.9, J101.12, J102.6, J102.9, J102.12, J102.15, J102.18, J102.19, J102.30, J103.4, J103.6, J202.1, J403.2, J502.1, J602.1, J702.1, J802.1, J902.1, J1002.1, Q402.2, Q503.2, Q505.3, Q506.2, Q603.2, Q605.3, Q606.2, Q703.2, Q705.3, Q706.2, Q803.2, Q805.3, Q806.2, Q903.2, Q905.3, Q906.2, Q1003.2, Q1005.3, Q1006.2, R209.2, R221.2, R302.2, R305.2, R306.2, R308.2, R311.2, R318.2, R322.2, R325.2, R402.2, R406.2, R409.2, R504.2, R506.2, R507.2, R510.2, R511.2, R518.2, R523.2, R523.3, R524.2, R525.2, R604.2, R606.2, R607.2, R610.2, R611.2, R618.2, R623.2, R623.3, R624.2, R625.2, R704.2, R706.2, R707.2, R710.2, R711.2, R718.2, R723.2, R723.3, R724.2, R725.2, R804.2, R806.2, R807.2, R810.2, R811.2, R818.2, R823.2, R823.3, R824.2, R825.2, R904.2, R906.2, R907.2, R910.2, R911.2, R918.2, R923.2, R923.3, R924.2, R925.2, R1004.2, R1006.2, R1007.2, R1010.2, R1011.2, R1018.2, R1023.2, R1023.3, R1024.2, R1025.2, RS1.4, RS401.4, RT102.2, U201.2, U201.7, U301.2, U301.6, U301.7, U301.10, U302.6, U302.7, U302.8, U302.9, U302.10, U401.4, U401.9, U402.2, U402.5, U403.2, U404.2, U404.4, U405.7, U501.5, U502.1, U502.2, U502.7, U503.2, U503.3, U503.4, U504.3, U601.5, U602.1, U602.7, U603.2, U603.3, U603.4, U604.3, U701.5, U702.2, U702.7, U703.2, U703.3, U703.4, U704.3, U801.5, U802.1, U802.7, U803.2, U803.3, U803.4, U804.3, U901.5, U902.7, U903.2, U903.3, U903.4, U904.3, U1001.5, U1002.7, U1003.2, U1003.3, U1003.4, U1004.3
I2C_AFE_SCL: J101.22, U1.26
I2C_AFE_SDA: J101.21, U1.27
I2C_HP_SCL: J101.27, U201.1, U201.5, U405.1, U405.5, U502.5, U602.5, U702.5, U802.2, U802.5, U902.2, U902.5, U1002.5
I2C_HP_SDA: J101.26, U201.4, U405.4, U502.4, U602.4, U702.4, U802.4, U902.4, U1002.4
IMON1: J102.20, R515.2
IMON2: J102.21, R615.2
IMON3: J102.22, R715.2
IMON4: J102.23, R815.2
IMON5: J102.24, R915.2
IMON6: J102.25, R1015.2
MID: C302.2, C306.1, Q301.2, Q302.3, Q303.2, Q304.3, Q305.2, Q306.3, R304.2, R318.1, R321.1, TP304.1, U301.13
MID_SENSE: J102.26, R323.2
NTC_BOARD1: J102.28, RT102.1
NTC_BRAKE: J102.29, J403.1
unnamed: C201.2, C202.1
unnamed: C208.2, C209.1
unnamed: D1.1, R15.1
unnamed: D202.2, R215.1
unnamed: D204.1, Q210.1, R218.1, R219.1
unnamed: D205.1, R219.2
unnamed: D209.1, R220.1
unnamed: Q201.1, R201.2
unnamed: Q202.1, R202.2
unnamed: Q203.1, R203.2
unnamed: Q204.1, R204.2
unnamed: Q205.1, R205.2
unnamed: Q206.1, R206.2
unnamed: Q207.1, R207.2
unnamed: Q208.1, R208.2
unnamed: R18.2, R19.1
unnamed: R20.2, R21.1
unnamed: R213.2, R214.1
unnamed: C19.1, U1.24
PORT_EN1: J101.15, Q504.1, R510.1
PORT_EN2: J101.16, Q604.1, R610.1
PORT_EN3: J101.17, Q704.1, R710.1
PORT_EN4: J101.18, Q804.1, R810.1
PORT_EN5: J101.19, Q904.1, R910.1
PORT_EN6: J101.20, Q1004.1, R1010.1
TS2_WAKE: J101.13, R23.2
VCLAMP12: C420.1, C422.1, C423.1, Q506.1, Q606.1, Q706.1, Q806.1, Q906.1, Q1006.1, R401.1, R403.1, R511.1, R611.1, R711.1, R811.1, R911.1, R1011.1, U401.1, U402.6, U404.1
VMOT: C305.2, C401.1, C402.1, C403.1, C404.1, C405.1, C406.1, C407.1, C408.1, C409.1, C410.1, C411.1, C412.1, C413.1, C414.1, C415.1, C416.1, C417.1, C418.1, C419.1, C501.1, C601.1, C701.1, C801.1, C901.1, C1001.1, D401.1, D402.1, D403.2, J401.1, Q302.2, Q304.2, Q306.2, Q307.2, R310.2, R320.2, R324.1, R404.1, R412.1, R503.1, R505.1, R509.1, R603.1, R605.1, R609.1, R703.1, R705.1, R709.1, R803.1, R805.1, R809.1, R903.1, R905.1, R909.1, R1003.1, R1005.1, R1009.1, RS501.1, RS601.1, RS701.1, RS801.1, RS901.1, RS1001.1, TP305.1, U302.13, U401.5, U401.8
VMOT_SENSE: J102.27, R326.2
VSS: C14.2, C15.2, C19.2, C20.2, C21.2, C22.2, C23.2, D15.2, D101.2, J2.3, NT1.2, R22.2, R102.2, RT101.2, U1.17, U1.36, U1.37
VSYS: C208.1, C210.1, D207.1, D220.3, J101.1, J101.2, J101.3, J101.4, J101.5, J101.6, Q301.3, Q303.3, Q305.3, R19.2, R21.2, R301.1, R307.1, RS201.4, TP101.1, TP201.1, TP303.1, U201.8
VSYS_SENS_N: RS201.3, U201.9, U301.17
VSYS_SENS_P: RS201.2, U201.10, U301.18
